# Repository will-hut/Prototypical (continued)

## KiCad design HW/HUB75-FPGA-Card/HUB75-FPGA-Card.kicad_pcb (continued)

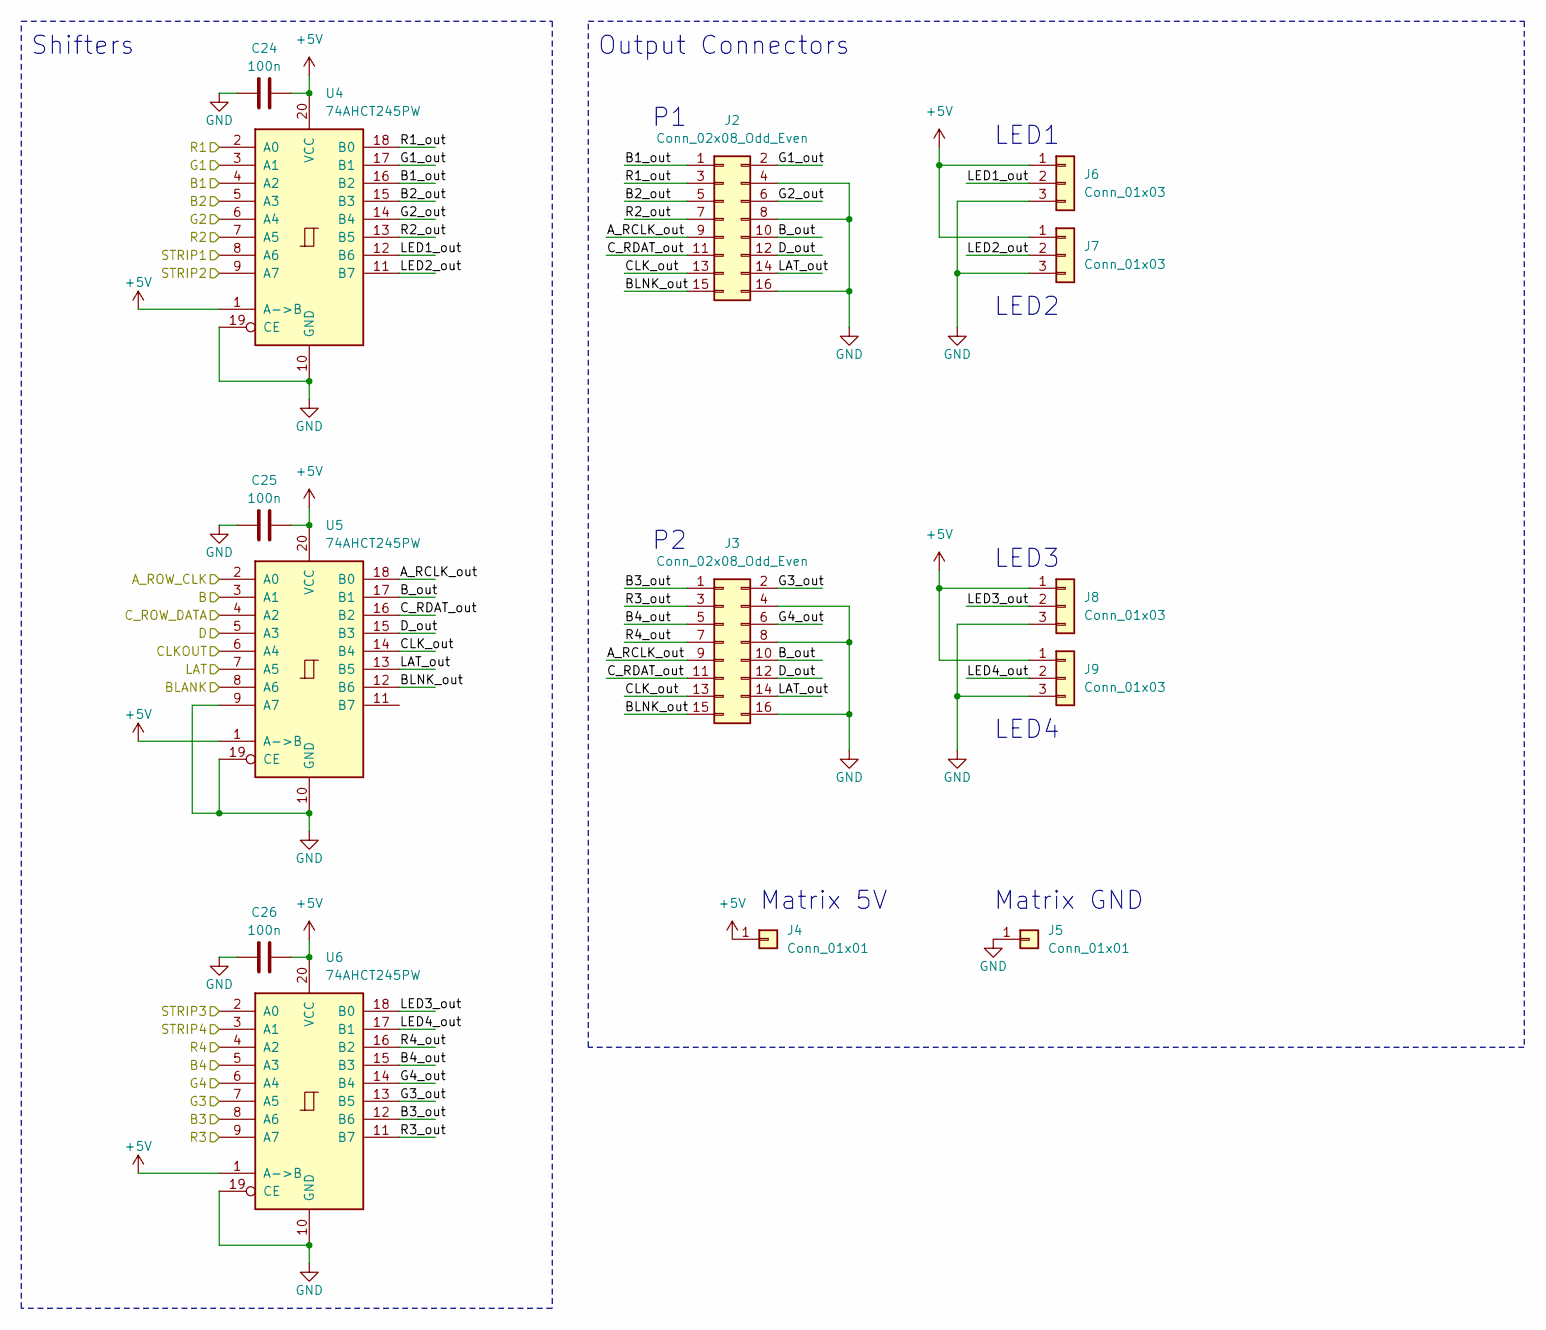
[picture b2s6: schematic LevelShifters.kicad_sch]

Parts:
C24, C25, C26: 100n; C_0603_1608Metric
J2, J3: Conn_02x08_Odd_Even; IDC-Header_2x08_P2.54mm_Vertical
J4, J5: Conn_01x01; SolderWire-2sqmm_1x01_D2mm_OD3.9mm
J6, J7, J8, J9: Conn_01x03; PinHeader_1x03_P2.54mm_Vertical
U4, U5, U6: 74AHCT245PW; TSSOP-20_4.4x6.5mm_P0.65mm

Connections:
+5V: C24.2, C25.2, C26.2, J4.1, J6.1, J7.1, J8.1, J9.1, U4.1 (A->B), U4.20 (VCC), U5.1 (A->B), U5.20 (VCC), U6.1 (A->B), U6.20 (VCC); also elsewhere on the board
/FPGA/A_ROW_CLK: U5.2 (A0); also elsewhere on the board
/FPGA/B: U5.3 (A1); also elsewhere on the board
/FPGA/B1: U4.4 (A2); also elsewhere on the board
/FPGA/B2: U4.5 (A3); also elsewhere on the board
/FPGA/B3: U6.8 (A6); also elsewhere on the board
/FPGA/B4: U6.5 (A3); also elsewhere on the board
/FPGA/BLANK: U5.8 (A6); also elsewhere on the board
/FPGA/CLKOUT: U5.6 (A4); also elsewhere on the board
/FPGA/C_ROW_DATA: U5.4 (A2); also elsewhere on the board
/FPGA/D: U5.5 (A3); also elsewhere on the board
/FPGA/G1: U4.3 (A1); also elsewhere on the board
/FPGA/G2: U4.6 (A4); also elsewhere on the board
/FPGA/G3: U6.7 (A5); also elsewhere on the board
/FPGA/G4: U6.6 (A4); also elsewhere on the board
/FPGA/LAT: U5.7 (A5); also elsewhere on the board
/FPGA/R1: U4.2 (A0); also elsewhere on the board
/FPGA/R2: U4.7 (A5); also elsewhere on the board
/FPGA/R3: U6.9 (A7); also elsewhere on the board
/FPGA/R4: U6.4 (A2); also elsewhere on the board
/FPGA/STRIP1: U4.8 (A6); also elsewhere on the board
/FPGA/STRIP2: U4.9 (A7); also elsewhere on the board
/FPGA/STRIP3: U6.2 (A0); also elsewhere on the board
/FPGA/STRIP4: U6.3 (A1); also elsewhere on the board
/Level Shifters/A_RCLK_out: J2.9, J3.9, U5.18 (B0)
/Level Shifters/B1_out: J2.1, U4.16 (B2)
/Level Shifters/B2_out: J2.5, U4.15 (B3)
/Level Shifters/B3_out: J3.1, U6.12 (B6)
/Level Shifters/B4_out: J3.5, U6.15 (B3)
/Level Shifters/BLNK_out: J2.15, J3.15, U5.12 (B6)
/Level Shifters/B_out: J2.10, J3.10, U5.17 (B1)
/Level Shifters/CLK_out: J2.13, J3.13, U5.14 (B4)
/Level Shifters/C_RDAT_out: J2.11, J3.11, U5.16 (B2)
/Level Shifters/D_out: J2.12, J3.12, U5.15 (B3)
/Level Shifters/G1_out: J2.2, U4.17 (B1)
/Level Shifters/G2_out: J2.6, U4.14 (B4)
/Level Shifters/G3_out: J3.2, U6.13 (B5)
/Level Shifters/G4_out: J3.6, U6.14 (B4)
/Level Shifters/LAT_out: J2.14, J3.14, U5.13 (B5)
/Level Shifters/LED1_out: J6.2, U4.12 (B6)
/Level Shifters/LED2_out: J7.2, U4.11 (B7)
/Level Shifters/LED3_out: J8.2, U6.18 (B0)
/Level Shifters/LED4_out: J9.2, U6.17 (B1)
/Level Shifters/R1_out: J2.3, U4.18 (B0)
/Level Shifters/R2_out: J2.7, U4.13 (B5)
/Level Shifters/R3_out: J3.3, U6.11 (B7)
/Level Shifters/R4_out: J3.7, U6.16 (B2)
GND: C24.1, C25.1, C26.1, J2.4, J2.8, J2.16, J3.4, J3.8, J3.16, J5.1, J6.3, J7.3, J8.3, J9.3, U4.10 (GND), U4.19 (CE), U5.9 (A7), U5.10 (GND), U5.19 (CE), U6.10 (GND), U6.19 (CE); also elsewhere on the board

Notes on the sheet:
LED1
Matrix GND
LED2
LED3
LED4
Matrix 5V
Output Connectors
Shifters

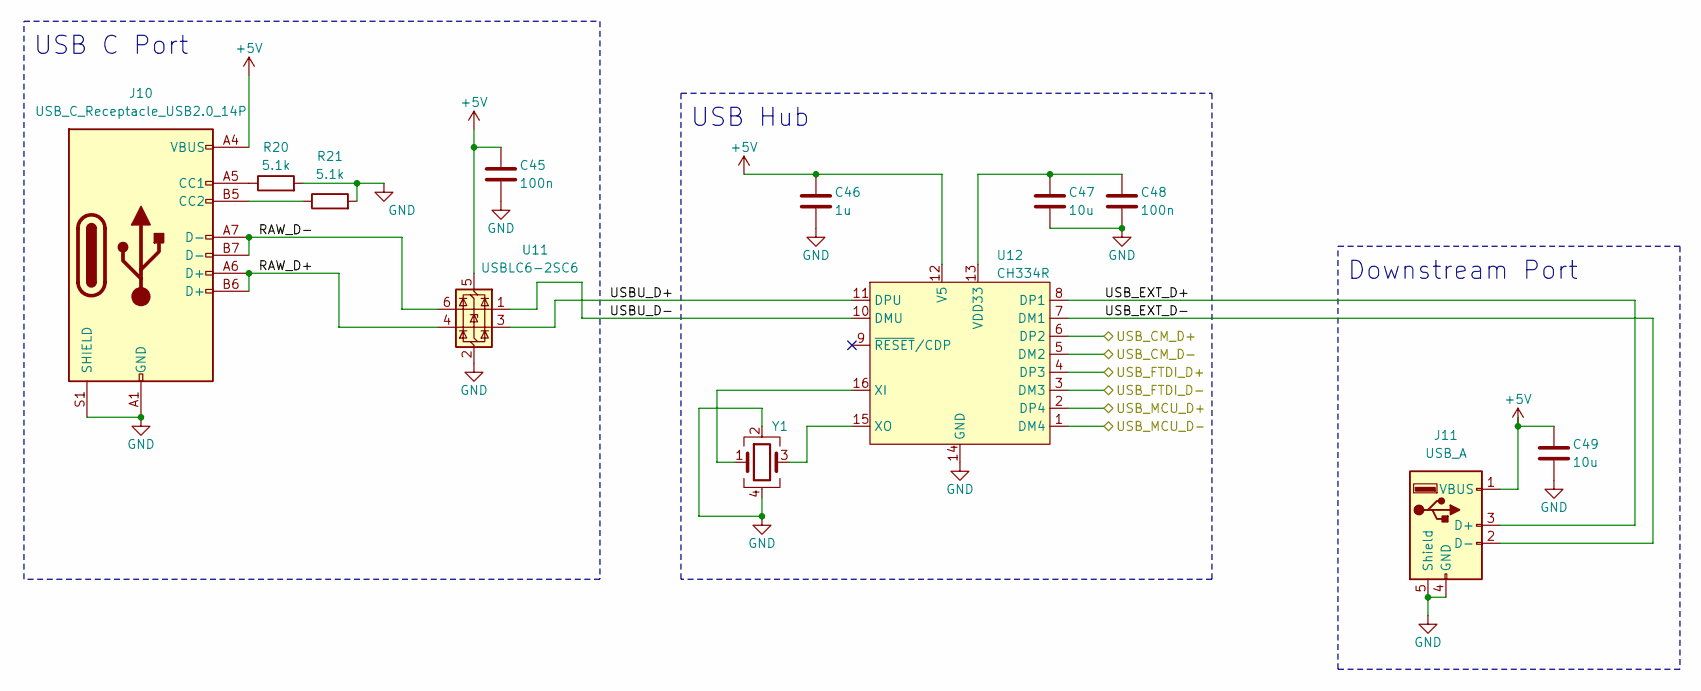
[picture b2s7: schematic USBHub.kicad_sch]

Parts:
C45, C48: 100n; C_0603_1608Metric
C46: 1u; C_0603_1608Metric
C47, C49: 10u; C_0603_1608Metric
J10: USB_C_Receptacle_USB2.0_14P; GCT_USB4145-03-0170-C_REVA2
J11: USB_A; SS-52100-002
R20, R21: 5.1k; R_0603_1608Metric
U11: USBLC6-2SC6; SOT-23-6
U12: CH334R; SSOP-16_3.9x4.9mm_P0.635mm; LCSC Part C4154405
Y1: Crystal_GND24; Crystal_SMD_3225-4Pin_3.2x2.5mm

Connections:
+5V: C45.1, C46.1, C49.1, J10.A4 (VBUS), J10.A9 (VBUS), J10.B4 (VBUS), J10.B9 (VBUS), J11.1 (VBUS), U11.5 (VBUS), U12.12 (V5); also elsewhere on the board
/FTDI/USB_D+: U12.4 (DP3); also elsewhere on the board
/FTDI/USB_D-: U12.3 (DM3); also elsewhere on the board
/MCU/USB_D+: U12.2 (DP4); also elsewhere on the board
/MCU/USB_D-: U12.1 (DM4); also elsewhere on the board
/USB Audio/USB_D+: U12.6 (DP2); also elsewhere on the board
/USB Audio/USB_D-: U12.5 (DM2); also elsewhere on the board
/USB Hub/RAW_D+: J10.A6 (D+), J10.B6 (D+), U11.4 (I/O2)
/USB Hub/RAW_D-: J10.A7 (D-), J10.B7 (D-), U11.6 (I/O1)
/USB Hub/USBU_D+: U11.3 (I/O2), U12.11 (DPU)
/USB Hub/USBU_D-: U11.1 (I/O1), U12.10 (DMU)
/USB Hub/USB_EXT_D+: J11.3 (D+), U12.8 (DP1)
/USB Hub/USB_EXT_D-: J11.2 (D-), U12.7 (DM1)
GND: C45.2, C46.2, C47.2, C48.2, C49.2, J10.A1 (GND), J10.A12 (GND), J10.B1 (GND), J10.B12 (GND), J10.S1 (SHIELD), J11.4 (GND), J11.5 (Shield), R20.2, R21.2, U11.2 (GND), U12.14 (GND), Y1.2, Y1.4; also elsewhere on the board
unnamed: J10.A5 (CC1), R20.1
unnamed: J10.B5 (CC2), R21.1
unnamed: C47.1, C48.1, U12.13 (VDD33)
unnamed: U12.16 (XI), Y1.1
unnamed: U12.15 (XO), Y1.3

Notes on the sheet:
USB Hub
USB C Port
Downstream Port

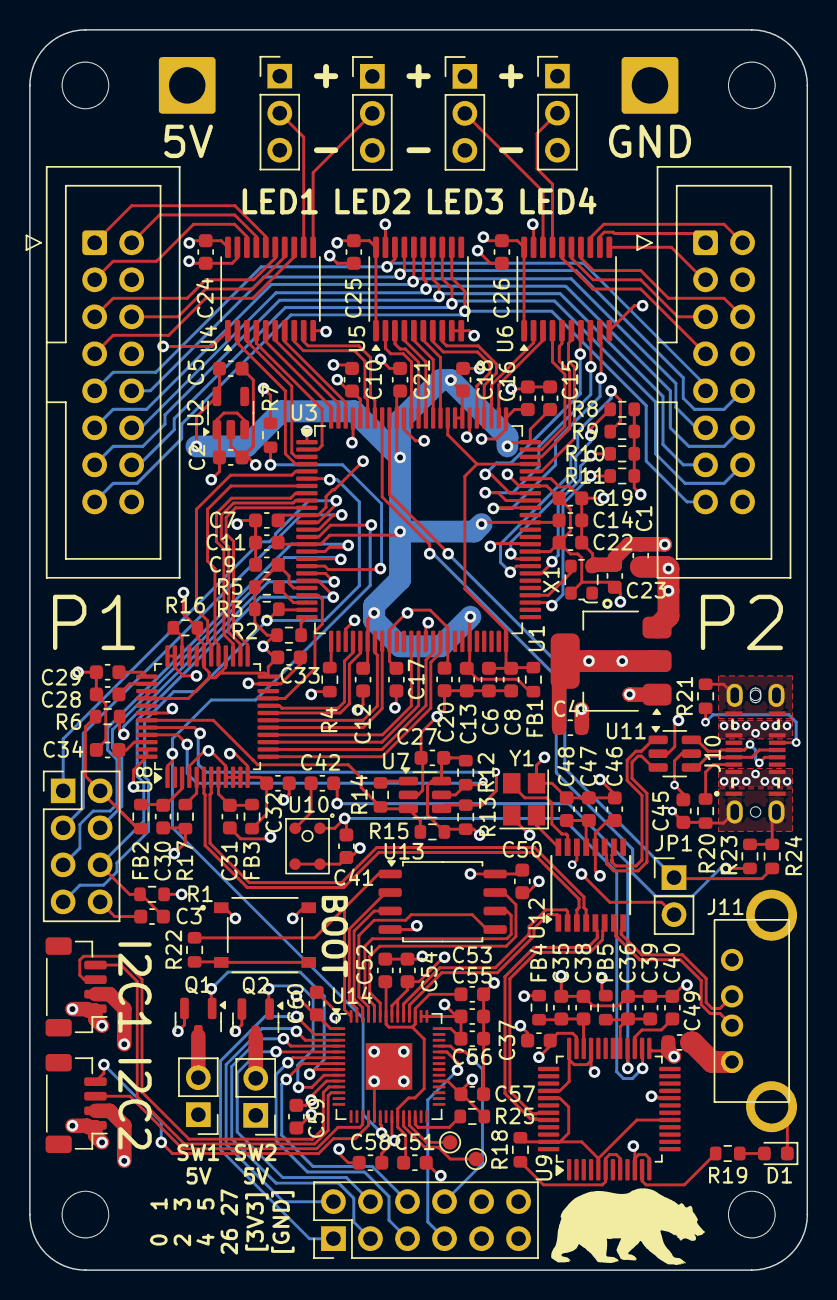
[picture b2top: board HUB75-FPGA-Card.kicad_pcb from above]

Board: 4 copper layers, 53.3 x 85.1 mm, 131 parts (0 on the bottom side), 148 nets.

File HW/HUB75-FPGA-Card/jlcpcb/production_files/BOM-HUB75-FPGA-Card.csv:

Comment,Designator,Footprint,LCSC
FerriteBead_Small,"FB1,FB2,FB3,FB4,FB5",R_0603_1608Metric,C1002
WMM7037AT2,U10,WMM7037AT2,C140705
100n,"C10,C13,C14,C15,C16,C17,C18,C19,C20,C21,C22,C23,C24,C25,C26,C27,C28,C29,C32,C33,C34,C37,C38,C39,C41,C45,C48,C50,C51,C52,C55,C56,C57,C58,C59,C6,C60,C7,C9",C_0603_1608Metric,C14663
1u,"C1,C12,C2,C42,C46,C5,C53,C54",C_0603_1608Metric,C15849
4.7u,"C3,C35,C36,C40,C8",C_0603_1608Metric,C19666
10u,"C11,C30,C31,C4,C47,C49",C_0603_1608Metric,C19702
RP2040,U14,QFN-56-1EP_7x7mm_P0.4mm_EP3.2x3.2mm,C2040
AO3400A,"Q1,Q2",SOT-23,C20917
12k,R17,R_0603_1608Metric,C22790
LED,D1,D_0603_1608Metric,C2286
5.1k,"R19,R20,R21",R_0603_1608Metric,C23186
10k,"R1,R10,R11,R12,R13,R15,R16,R18,R2,R23,R24,R25,R3,R4,R5,R6,R7,R8,R9",R_0603_1608Metric,C25804
SW_Push,SW1,SW_TS-1187A-B-A-B,C318884
HS-100B,U9,LQFP-48_7x7mm_P0.5mm,C371351
CH334R,U12,SSOP-16_3.9x4.9mm_P0.635mm,C4154405
2.2k,"R14,R22",R_0603_1608Metric,C4190
AMS1117-3.3,U1,SOT-223-3_TabPin2,C6186
Crystal_GND24,Y1,Crystal_SMD_3225-4Pin_3.2x2.5mm,C9002
W25Q128JVS,U13,SOIC-8_5.23x5.23mm_P1.27mm,C97521
MountingHole,H3,MountingHole_3.2mm_M3,
MountingHole,H2,MountingHole_3.2mm_M3,
FT232H,U8,LQFP-48_7x7mm_P0.5mm,
Conn_01x03,J6,PinHeader_1x03_P2.54mm_Vertical,
Conn_02x08_Odd_Even,J2,IDC-Header_2x08_P2.54mm_Vertical,
Conn_01x03,J7,PinHeader_1x03_P2.54mm_Vertical,
74AHCT245PW,U5,TSSOP-20_4.4x6.5mm_P0.65mm,
AP2112K-1.2,U2,SOT-23-5,
USB_A,J11,SS-52100-002,
Conn_01x03,J9,PinHeader_1x03_P2.54mm_Vertical,
74AHCT245PW,U6,TSSOP-20_4.4x6.5mm_P0.65mm,
Conn_02x06_Odd_Even,J12,PinHeader_2x06_P2.54mm_Vertical,
Conn_01x01,J5,SolderWire-2sqmm_1x01_D2mm_OD3.9mm,
Conn_01x01,J4,SolderWire-2sqmm_1x01_D2mm_OD3.9mm,
ECS-2520MV-xxx-xx,X1,Oscillator_SMD_ECS_2520MV-xxx-xx-4Pin_2.5x2.0mm,
USBLC6-2SC6,U11,SOT-23-6,
93LCxxBxxOT,U7,SOT-23-6,
Conn_01x03,J8,PinHeader_1x03_P2.54mm_Vertical,
MountingHole,H1,MountingHole_3.2mm_M3,
USB_C_Receptacle_USB2.0_14P,J10,GCT_USB4145-03-0170-C_REVA2,
Conn_02x04_Odd_Even,J1,PinHeader_2x04_P2.54mm_Vertical,
T20Q100F3,U3,TQFP-100_14x14mm_P0.5mm,
74AHCT245PW,U4,TSSOP-20_4.4x6.5mm_P0.65mm,
MountingHole,H4,MountingHole_3.2mm_M3,
Conn_02x08_Odd_Even,J3,IDC-Header_2x08_P2.54mm_Vertical,
Conn_01x02,J13,PinHeader_1x02_P2.54mm_Vertical,
Conn_01x02,J14,PinHeader_1x02_P2.54mm_Vertical,
Conn_01x04,J16,JST_SH_BM04B-SRSS-TB_1x04-1MP_P1.00mm_Vertical,
TestPoint,TP1,TestPoint_Pad_D1.0mm,
Conn_01x04,J17,JST_SH_BM04B-SRSS-TB_1x04-1MP_P1.00mm_Vertical,
TestPoint,TP2,TestPoint_Pad_D1.0mm,
Jumper_2_Open,JP1,PinHeader_1x02_P2.54mm_Vertical,

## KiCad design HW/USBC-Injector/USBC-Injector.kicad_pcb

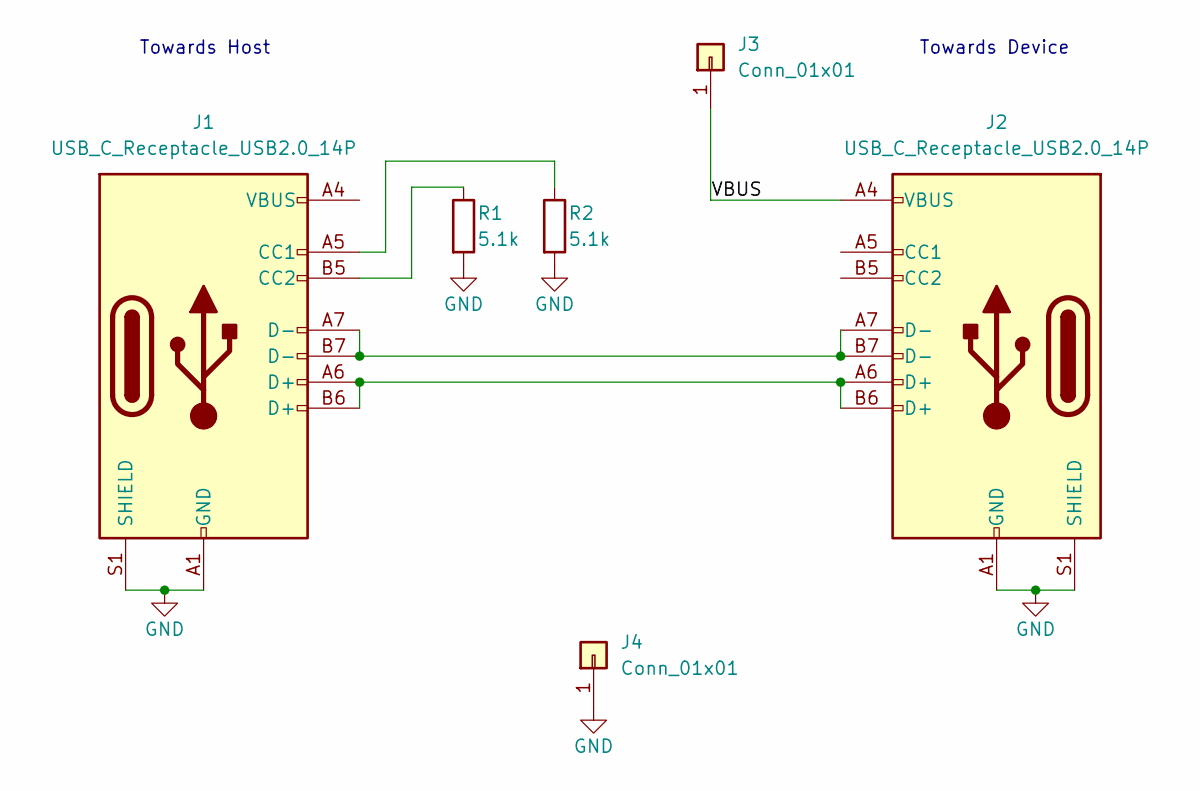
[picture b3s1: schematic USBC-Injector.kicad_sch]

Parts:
J1, J2: USB_C_Receptacle_USB2.0_14P; USB_C_Receptacle_GCT_USB4105-xx-A_16P_TopMnt_Horizontal
J3, J4: Conn_01x01; TestPoint_Keystone_5019_Minature
R1, R2: 5.1k; R_0603_1608Metric

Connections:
/VBUS: J2.A4 (VBUS), J2.A9 (VBUS), J2.B4 (VBUS), J2.B9 (VBUS), J3.1
GND: J1.A1 (GND), J1.A12 (GND), J1.B1 (GND), J1.B12 (GND), J1.S1 (SHIELD), J2.A1 (GND), J2.A12 (GND), J2.B1 (GND), J2.B12 (GND), J2.S1 (SHIELD), J4.1, R1.2, R2.2
unnamed: J1.A5 (CC1), R2.1
unnamed: J1.B5 (CC2), R1.1
unnamed: J1.A6 (D+), J1.B6 (D+), J2.A6 (D+), J2.B6 (D+)
unnamed: J1.A7 (D-), J1.B7 (D-), J2.A7 (D-), J2.B7 (D-)
unnamed: J1.A4 (VBUS), J1.A9 (VBUS), J1.B4 (VBUS), J1.B9 (VBUS)

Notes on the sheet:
Towards Host
Towards Device

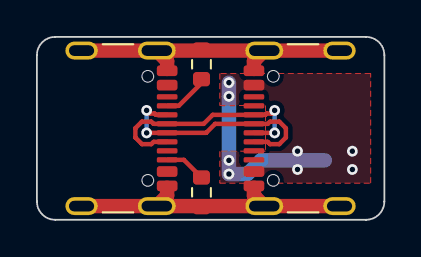
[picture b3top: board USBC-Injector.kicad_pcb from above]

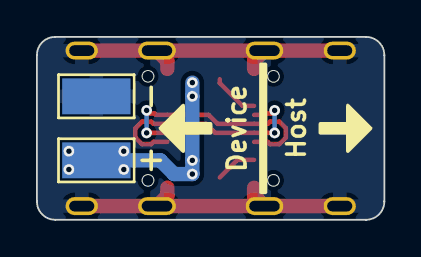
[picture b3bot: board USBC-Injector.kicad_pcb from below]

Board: 2 copper layers, 19.3 x 10.2 mm, 6 parts (2 on the bottom side), 7 nets.

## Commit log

2023-09-15 initial HDL commit
2023-09-20 implement max-brightness BCM delay logic
2023-09-20 fix my todo
2023-12-11 refactor to add registered outputs
2023-12-11 fix row select logic and implement lower brightness
    row select data bit may still be off by one
2023-12-11 fix row select, first successful test on FPGA
    yay
2023-12-20 add working read from framebuffer
    i'm so excited this works on the FPGA
2023-12-20 signal reordering and double buffer implementation
2023-12-23 add processing socket sender util
2023-12-23 create unix domain sockets sample program
2023-12-24 fix timing and add frame_start signal
2023-12-24 create MVP of ftdi sender program
2023-12-25 tidying
2023-12-25 slot ftdi module into main design/testbench for further development
2023-12-27 move buffer rearrangment logic to C program
    yet to be seen if this helps or hurts performance
2023-12-30 clean up hdl and improve ftdi testbench
2023-12-30 potential implementation of ftdi framebuffer writing and swapping
2023-12-30 ftdi frame input working successfully
    working proof of concept done yay
2024-01-03 update screen sender program to 64 bit and add systemd service
    Auto stash before revert of "update screen sender program to 64 bit and add systemd service"
2024-01-03 clean up HDL and add appropriate default buffer image
2024-01-05 move interlacing logic from C to FPGA
    image now contiguous in memory, and is accessed non-sequentially
2024-01-05 initial hardware commit
2024-01-05 update .gitignore for kicad
2024-01-05 provision address space for led strips
2024-01-05 add bram blocks for led strips
    compiles on FPGA
2024-01-16 add ws2812 led strip support
    all HDL in place now, yay
2024-01-22 add usb audio implementation
2024-01-22 rename Hub75 schematic page to LevelShifters
2024-01-23 finish up schematic and begin routing
2024-01-25 finalize pcb and generate production files for first run
2024-01-25 fix cross compile bug
2024-01-29 create (non compliant) usb c power injector
2024-01-29 improve portability of code
2024-01-29 rename ftdi-sender to senderservice
2024-01-29 first attempt of install script
2024-01-29 fix script and add readme
2024-01-29 create first working iteration of install script
2024-01-31 move verilog files to new folder
2024-02-01 add efinity projects and fix hdl typo
2024-02-01 beginning of board rev 1.1
2024-02-05 fix minor pcb annoyances
2024-02-08 fix install script
    missed an 'apt'
2024-02-08 saving hardware progress
2024-02-09 name change
2024-02-10 initial v1.1 board layout
    still needs rp2040 pins routed
2024-02-11 finish rp2040 routing
2024-02-12 update components and generate production files
    still need to look into CBSEL
2024-02-21 initial design for sbc 5v power board
2024-02-24 final v1.1 commit
    boards ordered
2024-02-26 migrate to kicad 8
2024-03-05 update matrix order and add efinity project file xmls
    gitignore excluded xmls
2024-03-08 Upload main Processing program/demo
    also improved socketsender
2024-03-08 improve connection code
    still need to handle serial reconnection
2024-03-09 improve main processing program
    add accelerometer reactions
2024-03-13 add emotions to main program
2026-05-05 Add pico firmware and improve processing sketch
